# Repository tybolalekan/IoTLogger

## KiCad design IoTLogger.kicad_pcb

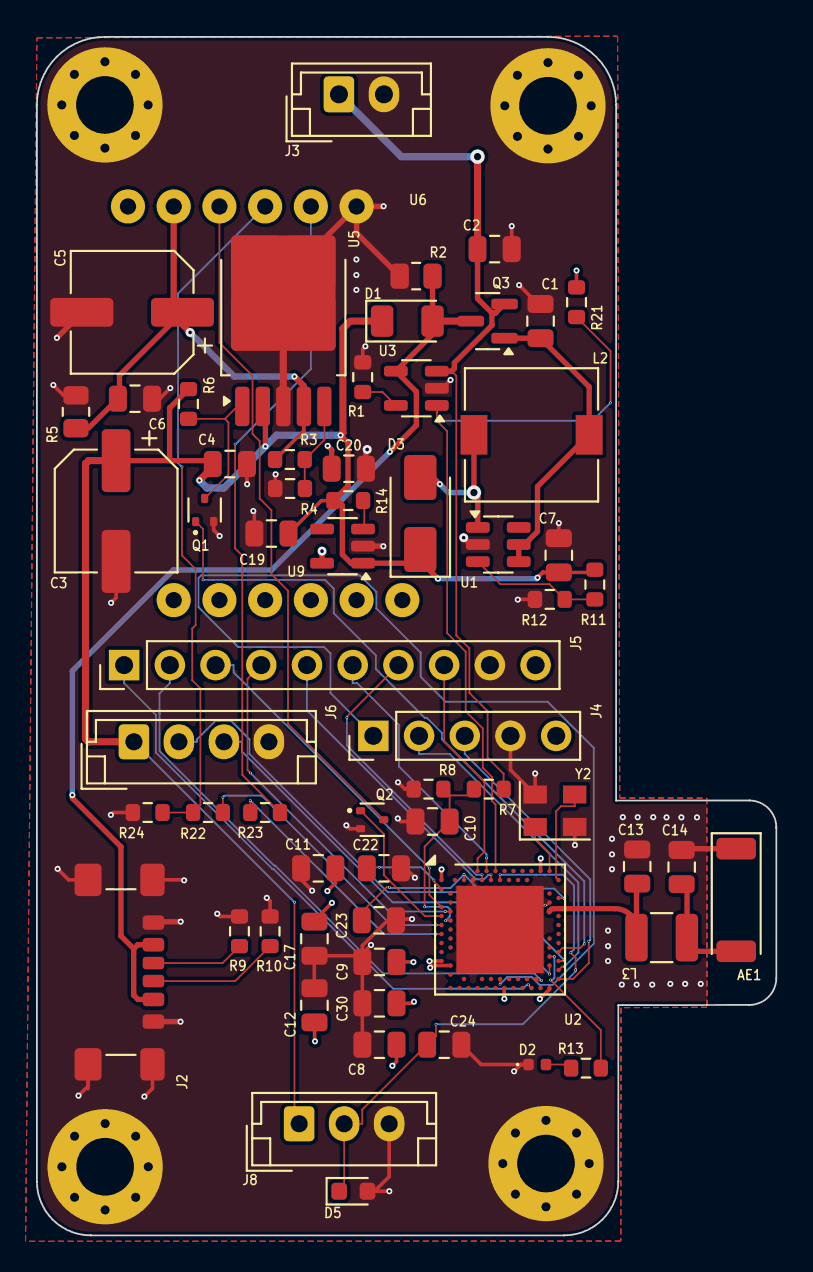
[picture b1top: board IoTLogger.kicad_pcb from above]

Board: 4 copper layers, 41.1 x 66.6 mm, 66 parts (1 on the bottom side), 46 nets.

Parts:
AE1: Antenna_Shield; Johanson_2450AT43F0100
C1, C7: 10u; C_0805_2012Metric
C2, C9: 4.7uF; C_0805_2012Metric
C3, C5: 100uF; CP_Elec_6.3x5.4
C4, C12, C17, C23: 1uF; C_0805_2012Metric
C6: 100nF; C_0805_2012Metric
C8, C11, C22, C24, C30: 0.1uF; C_0805_2012Metric
C10: 1nF; C_0805_2012Metric
C13: 0.8pF; C_0805_2012Metric
C14: 0.5pF; C_0805_2012Metric
C19, C20: 10uF; C_0805_2012Metric
D1: SD; D_1206_3216Metric
D2: LED; D_0402_1005Metric
D3: SS34; D_SMA
D5: 1.5KExxA; D_0603_1608Metric
H1, H2, H3, H4: Hole_Pad; MountingHole_3.2mm_M3_Pad_Via
J2: USB; USB_C_Receptacle_GCT_USB4135-GF-A_6P_TopMnt_Horizontal
J3: BATTERY; JST_EH_B2B-EH-A_1x02_P2.50mm_Vertical
J4: DEBUG; PinHeader_1x05_P2.54mm_Vertical
J5: EXT; PinHeader_1x10_P2.54mm_Vertical
J6: USENSOR; JST_EH_B4B-EH-A_1x04_P2.50mm_Vertical
J8: PSENSOR; JST_EH_B3B-EH-A_1x03_P2.50mm_Vertical
L2: 4.7uH; L_7.3x7.3_H3.5
L3: 4.7nH; L_1210_3225Metric
Q1, Q2: DTC143E; SOT-523
Q3: SOT-23
R1, R13, R22, R23: 1k; R_0603_1608Metric
R2: 100K; R_0805_2012Metric
R3, R14: 100k; R_0603_1608Metric
R4: 43k; R_0603_1608Metric
R5: 470R; R_0805_2012Metric
R6, R21: 10K; R_0603_1608Metric
R7: 806k; R_0603_1608Metric
R8: 2M; R_0603_1608Metric
R9: 5.1k; R_0603_1608Metric
R10: 5.1K; R_0603_1608Metric
R11: 110k; R_0603_1608Metric
R12: 15k; R_0603_1608Metric
R24: 5k6; R_0603_1608Metric
U1: MT3608; SOT-23-6
U2: nRF52840; Nordic_AQFN-73-1EP_7x7mm_P0.5mm
U3: MCP73831-2-OT; SOT-23-5
U5: MIC29302AWD; TO-252-5_TabPin3
U6: SIM800L; SIM800L-CORE
U9: AP2112K-3.3; SOT-23-5
Y2: 32mHZ; Crystal_SMD_EuroQuartz_MT-4Pin_3.2x2.5mm

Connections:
+5V: C3.1, C4.1, C7.2, C19.1, D1.1 (K), D3.1 (K), J6.1, J8.1, R6.2, R11.2, R14.2, U5.2 (VIN), U9.1 (VIN)
/Ba3: C2.1, J3.1, Q3.2 (D), R7.2, U3.3 (V_{BAT})
/CH_ST: R21.2, U2.A12 (AIN0/P0.02), U3.1 (STAT)
/NRF_LDO: Q1.1 (B), U2.U24 (P1.04)
/NRF_RST_KEY: Q2.1 (B), U2.J1 (AIN2/P0.04)
/PRESSURE: C24.2, D5.1 (A1), J8.2, U2.B13 (AIN1/P0.03)
/RST_KEY: Q2.3 (C), U6.3 (RST)
/RX1: J6.2, U2.W24 (P1.02)
/RX2: R23.1, U2.N1 (P0.08)
/RX_GSM: R22.2, R24.1, U6.4 (RXD)
/TX1: J6.3, U2.Y23 (P1.01)
/TX2: R22.1, U2.L1 (P0.06)
/TX_GSM: R23.2, U6.5 (TXD)
/VBAT: C1.2, L2.1, Q3.1 (S), U1.4 (EN), U1.5 (IN)
/VCC_MODEM: C5.1, C6.1, R3.2, R5.2, U5.4 (VOUT), U6.2 (VCC)
/VDD_NRF: C8.2, C9.2, C11.2, C12.2, C17.2, C20.1, C30.2, J4.5, J5.10, R21.1, U2.A22 (VDD), U2.AD14 (VDD), U2.AD23 (VDD), U2.B1 (VDD), U2.W1 (VDD), U2.Y2 (VDDH), U9.5 (VOUT)
/VIN: D1.2 (A), J2.A9 (VBUS), J2.B9 (VBUS), Q3.3 (G), R2.2, U3.4 (V_{DD})
GND: AE1.1 (A), C1.1, C2.2, C3.2, C4.2, C5.2, C6.2, C7.1, C8.1, C9.1, C10.1, C11.1, C12.1, C13.2, C14.2, C17.1, C19.2, C20.2, C22.2, C23.2, C24.1, C30.1, D2.1 (K), D5.2 (A2), H1.1, H2.1, H3.1, H4.1, J2.A12 (GND), J2.B12 (GND), J2.S1 (SHIELD), J3.2, J4.4, J5.9, J6.4, J8.3, Q1.2 (E), Q2.2 (E), R1.1, R2.1, R4.1, R5.1, R8.1, R9.2, R10.2, R12.1, R24.2, U1.2 (GND), U2.B7 (VSS), U2.EP (VSS), U2.F23 (VSS_PA), U3.2 (V_{SS}), U5.3 (GND), U6.6 (GND), U9.2 (GND), Y2.2, Y2.4
unnamed: AE1.2 (Shield), C14.1, L3.1
unnamed: D2.2 (A), R13.1
unnamed: D3.2 (A), L2.2, U1.1 (SW)
unnamed: J2.A5 (CC1), R9.1
unnamed: J2.B5 (CC2), R10.1
unnamed: J4.1, U2.AC13 (P0.18/~RESET)
unnamed: J4.2, U2.AA24 (SWDCLK)
unnamed: J4.3, U2.AC24 (SWDIO)
unnamed: J5.1, U2.AD20 (P0.24)
unnamed: J5.2, U2.AC21 (P0.25)
unnamed: J5.3, U2.G1 (P0.26)
unnamed: J5.4, U2.H2 (P0.27)
unnamed: J5.5, U2.B11 (AIN4/P0.28)
unnamed: J5.6, U2.A10 (AIN5/P0.29)
unnamed: J5.7, U2.B9 (AIN6/P0.30)
unnamed: J5.8, U2.A8 (AIN7/P0.31)
unnamed: Q1.3 (C), R6.1, U5.1 (EN)
unnamed: R11.1, R12.2, U1.3 (FB)
unnamed: C10.2, R7.1, R8.2, U2.K2 (AIN3/P0.05)
unnamed: C13.1, L3.2, U2.H23 (ANT)
unnamed: C22.1, U2.C1 (DEC1)
unnamed: C23.1, U2.B5 (DEC4), U2.E24 (DEC6)
unnamed: R13.2, U2.V23 (P1.03)
unnamed: U2.B24 (XC1), Y2.3
unnamed: U2.A23 (XC2), Y2.1
unnamed: R1.2, U3.5 (PROG)
unnamed: R3.1, R4.2, U5.5 (ADJ)
unnamed: R14.1, U9.3 (EN)

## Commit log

2024-11-08 Initial Commit
    Initial Commit
